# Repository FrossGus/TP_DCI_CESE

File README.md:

# TP_DCI_CESE
Trabajo Practico de Diseño de Circuitos Impresos de la CESE

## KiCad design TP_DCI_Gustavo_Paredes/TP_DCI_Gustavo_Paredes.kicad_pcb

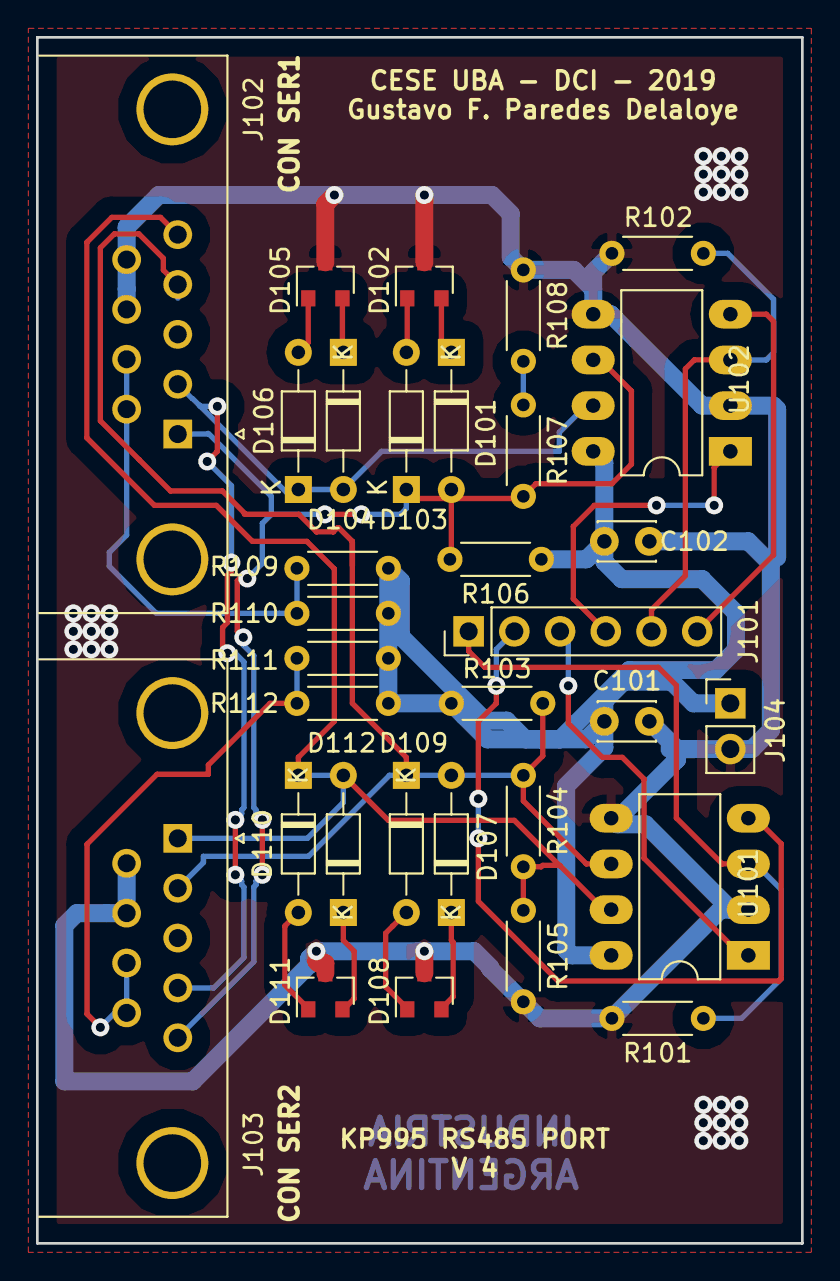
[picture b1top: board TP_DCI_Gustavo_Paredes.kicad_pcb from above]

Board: 2 copper layers, 42.5 x 67.0 mm, 32 parts (0 on the bottom side), 23 nets.

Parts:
C101, C102: 22nF; C_Disc_D3.0mm_W2.0mm_P2.50mm
D101, D104, D107, D110: BZX84C4V7; D_DO-34_SOD68_P7.62mm_Horizontal
D102, D105, D108, D111: BAV99; SOT-23
D103, D106, D109, D112: BZX84C8V2; D_DO-34_SOD68_P7.62mm_Horizontal
J101: Conector; PinHeader_1x06_P2.54mm_Vertical
J102: DB9 Hembra; DSUB-9_Female_Horizontal_P2.77x2.84mm_EdgePinOffset4.94mm_H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
J103: DB9 Macho; DSUB-9_Male_Horizontal_P2.77x2.84mm_EdgePinOffset4.94mm_Hou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
J104: Conector +5V; PinHeader_1x02_P2.54mm_Vertical
R101, R102: 10K; R_Axial_DIN0204_L3.6mm_D1.6mm_P5.08mm_Horizontal
R103, R105, R106, R108: 68K; R_Axial_DIN0204_L3.6mm_D1.6mm_P5.08mm_Horizontal
R104, R107: 27K; R_Axial_DIN0204_L3.6mm_D1.6mm_P5.08mm_Horizontal
R109, R110, R111, R112: 10R; R_Axial_DIN0204_L3.6mm_D1.6mm_P5.08mm_Horizontal
U101, U102: LTC1485; DIP-8_W7.62mm_LongPads

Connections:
+5V: C101.1, C102.1, J104.1, R103.1, R106.1, R109.1, R110.1, R111.1, R112.1, U101.8, U102.8
/A_Data_N: D107.2, D109.1, J102.4, J103.2, R103.2, R104.1, U101.6
/A_Data_P: D110.2, D112.1, J102.5, J103.1, R104.2, R105.1, U101.7
/B_Data_N: D101.2, D103.1, J102.1, J103.5, R106.2, R107.1, U102.6
/B_Data_P: D104.2, D106.1, J102.2, J103.4, U102.7
/LINE_A_D0: J101.2, U101.4
/LINE_A_D1: J101.3, U101.1
/LINE_A_SF: J101.1, R101.1, U101.3
/LINE_B_D0: J101.6, U102.4
/LINE_B_D1: J101.4, U102.1
/LINE_B_SF: J101.5, R102.1, U102.3
GNDD: C101.2, C102.2, D102.3, D105.3, D108.3, D111.3, J102.8, J102.9, J103.6, J103.7, J104.2, R101.2, R102.2, R105.2, R108.2, U101.2, U101.5, U102.2, U102.5
unnamed: D101.1, D102.2
unnamed: D102.1, D103.2
unnamed: D104.1, D105.2
unnamed: D105.1, D106.2
unnamed: D107.1, D108.2
unnamed: D108.1, D109.2
unnamed: D110.1, D111.2
unnamed: D111.1, D112.2
unnamed: J102.6, J102.7, R109.2, R110.2
unnamed: J103.8, J103.9, R111.2, R112.2
unnamed: R107.2, R108.1

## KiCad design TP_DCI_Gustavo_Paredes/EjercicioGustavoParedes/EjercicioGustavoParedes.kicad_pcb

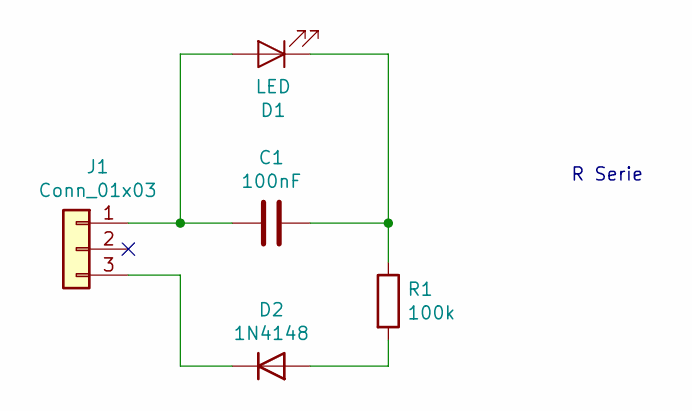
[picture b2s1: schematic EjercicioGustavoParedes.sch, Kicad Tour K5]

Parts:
C1: 100nF; CP_Radial_D4.0mm_P2.00mm
D1: LED; LED_D3.0mm
D2: 1N4148; D_5W_P10.16mm_Horizontal
J1: Conn_01x03; PinHeader_1x03_P1.00mm_Vertical
R1: 100k; R_Axial_DIN0204_L3.6mm_D1.6mm_P1.90mm_Vertical

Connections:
unnamed: C1.1, D1.2 (A), J1.1
unnamed: C1.2, D1.1 (K), R1.1
unnamed: D2.1 (A), R1.2
unnamed: D2.2 (K), J1.3

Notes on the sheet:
R Serie

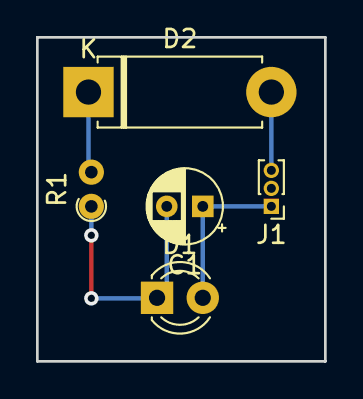
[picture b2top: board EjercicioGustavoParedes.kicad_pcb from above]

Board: 2 copper layers, 16.0 x 18.0 mm, 5 parts (0 on the bottom side), 4 nets.

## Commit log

2019-05-21 Esquematico elegido subido a repo
    En este commit se ha realizado lo siguiente:
    * Se imprimio la pagina siete, la cual contiene el esqumatico elegido para la materia.
2019-05-21 Creamos Proyecto
    Creamos el Proyecto TP_DCI_Gustavo_Paredes
2019-05-21 Conector DB9
    Conector DB9 casi listo.
2019-05-21 Conecciones externas DB9
    Se conectaron las conexiones externas del DB9.
2019-05-22 Archivos Clase 4
    Se agregaron los archivos (en una carpeta) del ejercicio de la clase 4 sobre inicio con KiCAD.
2019-05-28 Agrego Ejercicio
    Ejercicio de la clase 4 y 5
2019-05-29 1er Version
    Primera version del ejercicio aulico.
2019-05-29 Clase 5 completa
    Ruteo, Puente, Recuadro.
2019-06-17 Saco Ejercicios Practica Clases
    Saco a un carpeta externa los ejercicios de las clases.
2019-06-18 Arreglo algunos Errores electricos
    Se repararon algunos errores del chequeo electrico, pero no todos.
2019-06-18 Cambios Corrector
    Realize los cambios propuestos por el compañero corrector.
2019-06-18 Cambios Diodos Rapidos
    Pequeños cambios en los diodos rapidos BVA99 que me arrojaban errores electricos porque vienen de a pares.
2019-06-18 Coneccion faltante.
    Agregue una pequeña conexión faltante.
2019-06-27 Arreglo Etiqueta Global
    Arregle la etiqueta global para que pase el ERC. Pero sigo con problemas en otros puntos.
2019-07-02 Arreglos sugeridos x Docente
    Realize los arreglos sugeridos por el Docente en la planilla.
2019-07-02 Arreglos PDFs
    Arregle nombres archivos PDFs de hoja de datos.
2019-07-02 Valores R/Huellas y Conector 6 Pines
    Agregue valores a 3 R que faltaban, Huella de las mismas y del conector de 6 pines.
2019-07-02 Agregue Conector VCC
    Agregue conector para 5V y GND. Ya esta hecha la distribucion basica de componentes en el PCB. Recargo la NETList.
2019-07-03 Correcciones Esquematico V3
    Se realizaron las correcciones menores que el Docente indico. Se actualizo huella y 3D del LTC1485 y los dos DB9.
2019-07-04 Se ruteo el PCB
    Primer intento de ruteo.
2019-07-05 PCB V1
    Se termina V1 del PCB a la espera de las correcciones.
2019-07-05 Correccion texto
    Pequeño corrimiento del texto solapado con la cota.
2019-07-08 Correccion Esquematico
    Correccion del esquematico en conector J104.
2019-07-08 PCB V4
    Se aplicarons las correciones del Docente.

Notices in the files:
TP_DCI_Gustavo_Paredes/TP_DCI_Gustavo_Paredes.kicad_pcb:
Licencia: GPL
